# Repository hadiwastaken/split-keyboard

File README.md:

# split keyboard

**what it it:**

* so basically it is an split keyboard and has 15 keys on each side and design to comfort the user and also to understand matrix system i use esp32wroom32D development boards and make a custum firmware and i forget to tell you that it operates wirelessly.

**FEATURES:**

* IT features an Esp 32 development board because its cheap and easily available on any online hardware store.
* it has 15 keys on each sides.
* it features wireless communication
* it has diodes to prevent from ghosting.
* i use hierarchal sheets in schematics for not wasting time\
* i also pick one of the best pins on esp32 module.
* its PCB offers breakoff

**IMAGES:**

**MAIN ROOT PAGE:**

**LEFT SIDE:**

**RIGHT SIDE:**

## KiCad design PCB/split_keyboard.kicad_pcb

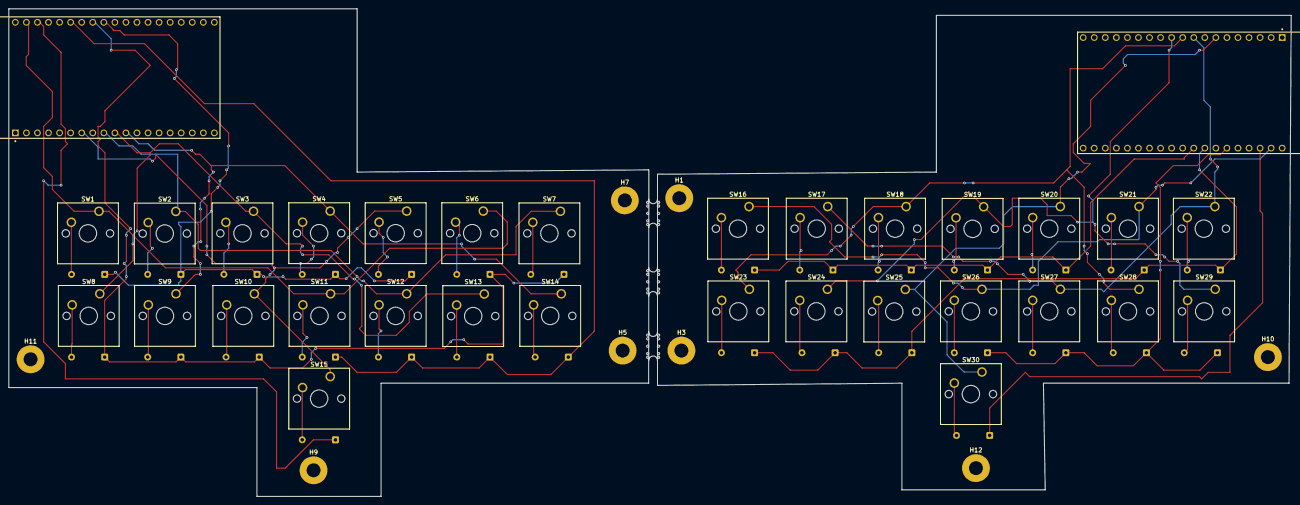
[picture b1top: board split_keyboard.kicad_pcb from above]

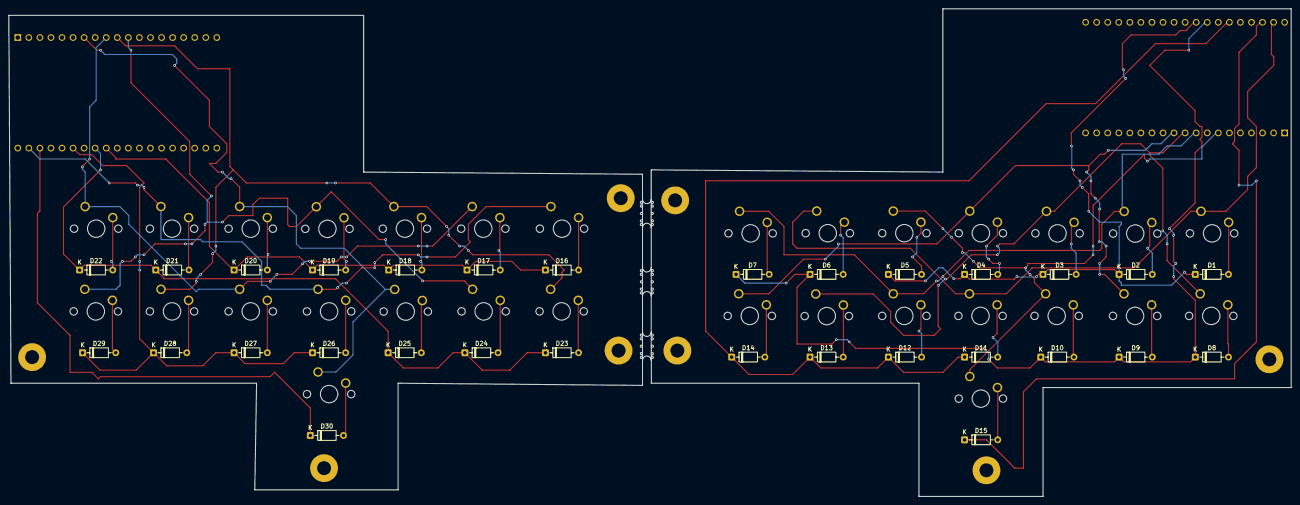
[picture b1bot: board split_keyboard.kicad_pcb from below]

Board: 2 copper layers, 294.6 x 112.0 mm, 73 parts (30 on the bottom side), 48 nets.

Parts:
B01, B02, B03: MouseBite-Slot_2.0x4.5mm_inset_D0.5mm_P0.85mm_5h_Trace
D1, D2, D3, D4, D5, D6, D7, D8, D9, D10, D11, D12, D13, D14, D15, D16, D17, D18, D19, D20, D21, D22, D23, D24, D25, D26, D27, D28, D29, D30: D; D_DO-35_SOD27_P7.62mm_Horizontal
H1, H3, H5, H7, H9, H10, H11, H12: MountingHole_3.2mm_M3_Pad
SW1, SW2, SW3, SW4, SW5, SW6, SW7, SW8, SW9, SW10, SW11, SW12, SW13, SW14, SW15, SW16, SW17, SW18, SW19, SW20, SW21, SW22, SW23, SW24, SW25, SW26, SW27, SW28, SW29, SW30: SW_Push; SW_Cherry_MX_1.00u_PCB
U1, U2: ESP32-DEVKITC-32D; MODULE_ESP32-DEVKITC-32D

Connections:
/left/COL0: SW1.1, SW6.1, SW11.1, U1.J3-2 (IO23)
/left/COL1: SW2.1, SW7.1, SW12.1, U1.J2-9 (IO25)
/left/COL2: SW3.1, SW8.1, SW13.1, U1.J2-10 (IO26)
/left/COL3: SW4.1, SW9.1, SW14.1, U1.J2-11 (IO27)
/left/COL4: SW5.1, SW10.1, SW15.1, U1.J2-7 (IO32)
/left/ROW0: D1.1 (K), D2.1 (K), D3.1 (K), D4.1 (K), D5.1 (K), U1.J3-9 (IO18)
/left/ROW1: D6.1 (K), D7.1 (K), D8.1 (K), D9.1 (K), D10.1 (K), U1.J3-8 (IO19)
/left/ROW2: D11.1 (K), D12.1 (K), D13.1 (K), D14.1 (K), U1.J3-6 (IO21)
/left/ROW3: D15.1 (K), U1.J3-3 (IO22)
/right/COL0: SW16.1, SW21.1, SW26.1, U2.J3-2 (IO23)
/right/COL1: SW17.1, SW22.1, SW27.1, U2.J2-9 (IO25)
/right/COL2: SW18.1, SW23.1, SW28.1, U2.J2-10 (IO26)
/right/COL3: SW19.1, SW24.1, SW29.1, U2.J2-11 (IO27)
/right/COL4: SW20.1, SW25.1, SW30.1, U2.J2-7 (IO32)
/right/ROW0: D16.1 (K), D17.1 (K), D18.1 (K), D19.1 (K), D20.1 (K), U2.J3-9 (IO18)
/right/ROW1: D21.1 (K), D22.1 (K), D23.1 (K), D24.1 (K), D25.1 (K), U2.J3-8 (IO19)
/right/ROW2: D26.1 (K), D27.1 (K), D28.1 (K), D29.1 (K), U2.J3-6 (IO21)
/right/ROW3: D30.1 (K), U2.J3-3 (IO22)
unnamed: D1.2 (A), SW1.2
unnamed: D2.2 (A), SW2.2
unnamed: D3.2 (A), SW3.2
unnamed: D4.2 (A), SW4.2
unnamed: D5.2 (A), SW5.2
unnamed: D6.2 (A), SW6.2
unnamed: D7.2 (A), SW7.2
unnamed: D8.2 (A), SW8.2
unnamed: D9.2 (A), SW9.2
unnamed: D10.2 (A), SW10.2
unnamed: D11.2 (A), SW11.2
unnamed: D12.2 (A), SW12.2
unnamed: D13.2 (A), SW13.2
unnamed: D14.2 (A), SW14.2
unnamed: D15.2 (A), SW15.2
unnamed: D16.2 (A), SW16.2
unnamed: D17.2 (A), SW17.2
unnamed: D18.2 (A), SW18.2
unnamed: D19.2 (A), SW19.2
unnamed: D20.2 (A), SW20.2
unnamed: D21.2 (A), SW21.2
unnamed: D22.2 (A), SW22.2
unnamed: D23.2 (A), SW23.2
unnamed: D24.2 (A), SW24.2
unnamed: D25.2 (A), SW25.2
unnamed: D26.2 (A), SW26.2
unnamed: D27.2 (A), SW27.2
unnamed: D28.2 (A), SW28.2
unnamed: D29.2 (A), SW29.2
unnamed: D30.2 (A), SW30.2

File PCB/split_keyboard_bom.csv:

Designator,Footprint,Quantity,Value,LCSC Part #
"D1, D10, D11, D12, D13, D14, D15, D16, D17, D18, D19, D2, D20, D21, D22, D23, D24, D25, D26, D27, D28, D29, D3, D30, D4, D5, D6, D7, D8, D9",D_DO-35_SOD27_P7.62mm_Horizontal,30,D,
"SW1, SW10, SW11, SW12, SW13, SW14, SW15, SW16, SW17, SW18, SW19, SW2, SW20, SW21, SW22, SW23, SW24, SW25, SW26, SW27, SW28, SW29, SW3, SW30, SW4, SW5, SW6, SW7, SW8, SW9",SW_Cherry_MX_1.00u_PCB,30,SW_Push,
"U1, U2",MODULE_ESP32-DEVKITC-32D,2,ESP32-DEVKITC-32D,
